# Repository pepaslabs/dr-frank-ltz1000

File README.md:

# dr-frank-ltz1000

This is Dr. Frank's LTZ1000-based 10V reference design.

You can order a copy of this board from OSHPark here: [link](https://oshpark.com/shared_projects/dGYcQAgn)

Alternatively, you can use the gerber files to have the board made somewhere else: [gerbers.zip](kicad/releases/v1/gerbers.zip)

Dr. Frank's discussion of his design: [link](http://www.eevblog.com/forum/metrology/mx-reference/msg1297126/#msg1297126).

Dr. Frank's schematic: [jpg](media/LTZ_schematics.jpg)

My recreation of the schematic in kicad: [pdf](kicad/releases/v1/drfrank-ltz1000.pdf)

Dr. Frank's board layout: [jpg](media/LTZ_board.jpg)

I recreated his board layout by importing the jpg of his board design into kicad and matching the layout: [png](media/Screen%20Shot%202017-12-16%20at%202.52.52%20AM.png)

My post to the EEVBlog forum about this recreation: [link](http://www.eevblog.com/forum/metrology/ultra-precision-reference-ltz1000/msg1376260/#msg1376260)

See also: https://github.com/pepaslabs/px-ref

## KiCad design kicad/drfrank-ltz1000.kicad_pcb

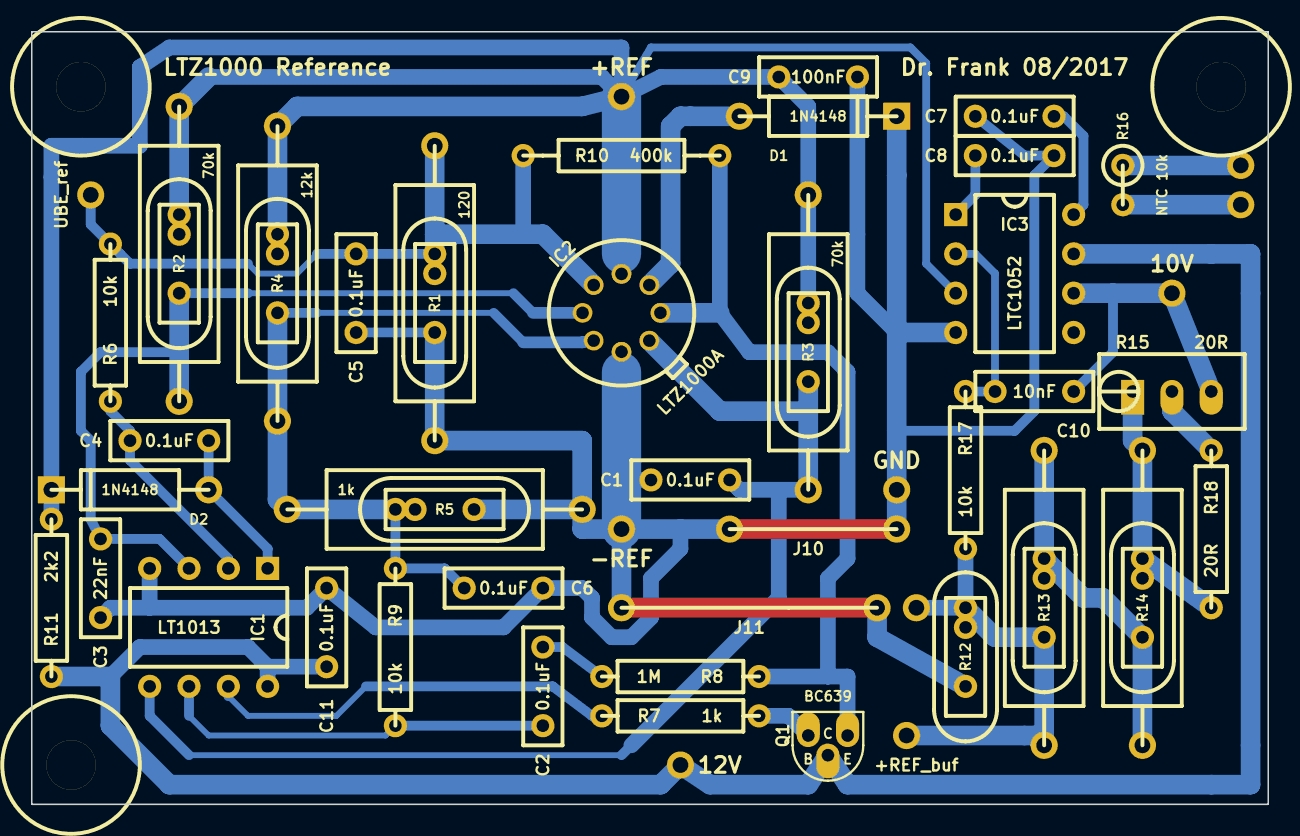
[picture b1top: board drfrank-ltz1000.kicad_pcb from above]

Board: 2 copper layers, 79.9 x 49.9 mm, 57 parts (0 on the bottom side), 25 nets.

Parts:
C1, C2, C4, C5, C6, C7, C8, C11: 0.1uF; BOXCAP_01_03_02_059A
C3: 22nF; BOXCAP_01_03_02_059A
C9: 100nF; BOXCAP_01_03_02_059A
C10: 10nF; BOXCAP_01_03_02_059A
D1, D2: 1N4148; DIODE_1A_069A_PL
H***: Val**; hole_M3_2
H***#2, H***#3: Val**; hole_M3_2
IC1: LT1013; DIP8_059A_PL
IC2: LTZ1000A; TO-99_PL
IC3: LTC1052; DIP8_059A_PL
J10: LINK; LINK_069A_0425_PL
J11: LINK; LINK_069A_065_PL
JP1, JP2, JP3, JP4, JP5, JP6, JP7, JP8, JP9, JP12: CONN_1X1; 1pin_040_069
Q1: BC639; TO-92_Q_ECB_059Bo_PL
R1: 120; R_BOX_PL
R2, R3: 70k; R_BOX_PL
R4: 12k; R_BOX_PL
R5: 1k; R_BOX_PL
R6, R9, R17: 10k; R_AXIAL_0W25_059A_PL
R7: 1k; R_AXIAL_0W25_059A_PL
R8: 1M; R_AXIAL_0W25_059A_PL
R10: 400k; R_AXIAL_0W25_059A_05_PL
R11: 2k2; R_AXIAL_0W25_059A_PL
R12: 15k; R_BOX_PL
R13: 5k6; R_BOX_PL
R14: 0..500; R_BOX_PL
R15: 20R; 3296W_PL
R16: NTC 10k; R_AXIAL_0W25_V_059A_PL
R18: 20R; R_AXIAL_0W25_059A_PL
R20, R30: 70k; R_AXIAL_WW_069A_075_PL
R40: 12k; R_AXIAL_WW_069A_075_PL
R50: 1k; R_AXIAL_WW_069A_075_PL
R100: 120; R_AXIAL_WW_069A_075_PL
R130: 4k; R_AXIAL_WW_069A_075_PL
R140: 0..250; R_AXIAL_WW_069A_075_PL

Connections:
10.00000V: C10.2, IC3.6, JP4.1, R15.3
12V: C11.1, IC1.8, IC3.7, JP3.1, Q1.2, R11.1
+REF: C9.1, D2.2, IC2.3, IC3.3, JP8.1, R2.1, R3.1, R4.1, R11.2, R20.1, R30.1, R40.1
+REF_buf: JP9.1, JP12.1, R12.1, R13.2, R17.2, R130.2
-REF: C1.2, C3.2, C5.2, C6.2, C7.2, C8.2, C9.2, C11.2, D1.2, IC1.4, IC2.7, IC3.4, J10.1, J10.2, J11.1, J11.2, JP1.1, JP2.1, R1.2, R5.2, R12.2, R50.2, R100.2
H+: IC2.1, Q1.1, R8.1, R10.2
unnamed: C7.1, IC3.1
unnamed: C8.1, IC3.8
unnamed: R15.2, R18.1
unnamed: C10.1, IC3.2, R17.1
unnamed: D1.1, IC2.2
unnamed: C1.1, IC1.5, IC2.8, R3.2, R30.2
unnamed: C2.2, R8.2
unnamed: C2.1, IC1.6, R9.2
unnamed: R14.1, R15.1, R18.2, R140.1
unnamed: R13.1, R14.2, R130.1, R140.2
unnamed: C4.2, D2.1, IC1.1
unnamed: Q1.3, R7.2
unnamed: IC1.7, R7.1
unnamed: C3.1, IC1.3, IC2.5, R2.2, R20.2
unnamed: C4.1, IC1.2, R6.1
unnamed: C6.1, IC2.6, R4.2, R5.1, R9.1, R40.2, R50.1
unnamed: JP6.1, R16.2
unnamed: JP5.1, R16.1
UBE_ref: C5.1, IC2.4, JP7.1, R1.1, R6.2, R10.1, R100.1

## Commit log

2017-12-16 initial import
2017-12-16 Pulling in Dr. Frank's published materials
2017-12-16 pulling in kicad screenshot
2017-12-16 moving copper to back side, adding copper links
2017-12-16 updating gerbers.zip and board shots
2017-12-16 Omit D3. Correct R5 label.
2017-12-16 Updating board shots and gerbers.zip
2018-04-30 MAX420 -> LTC1052
2018-04-30 using updated TO-99 footprint
2018-04-30 board shots
2018-04-30 readme
